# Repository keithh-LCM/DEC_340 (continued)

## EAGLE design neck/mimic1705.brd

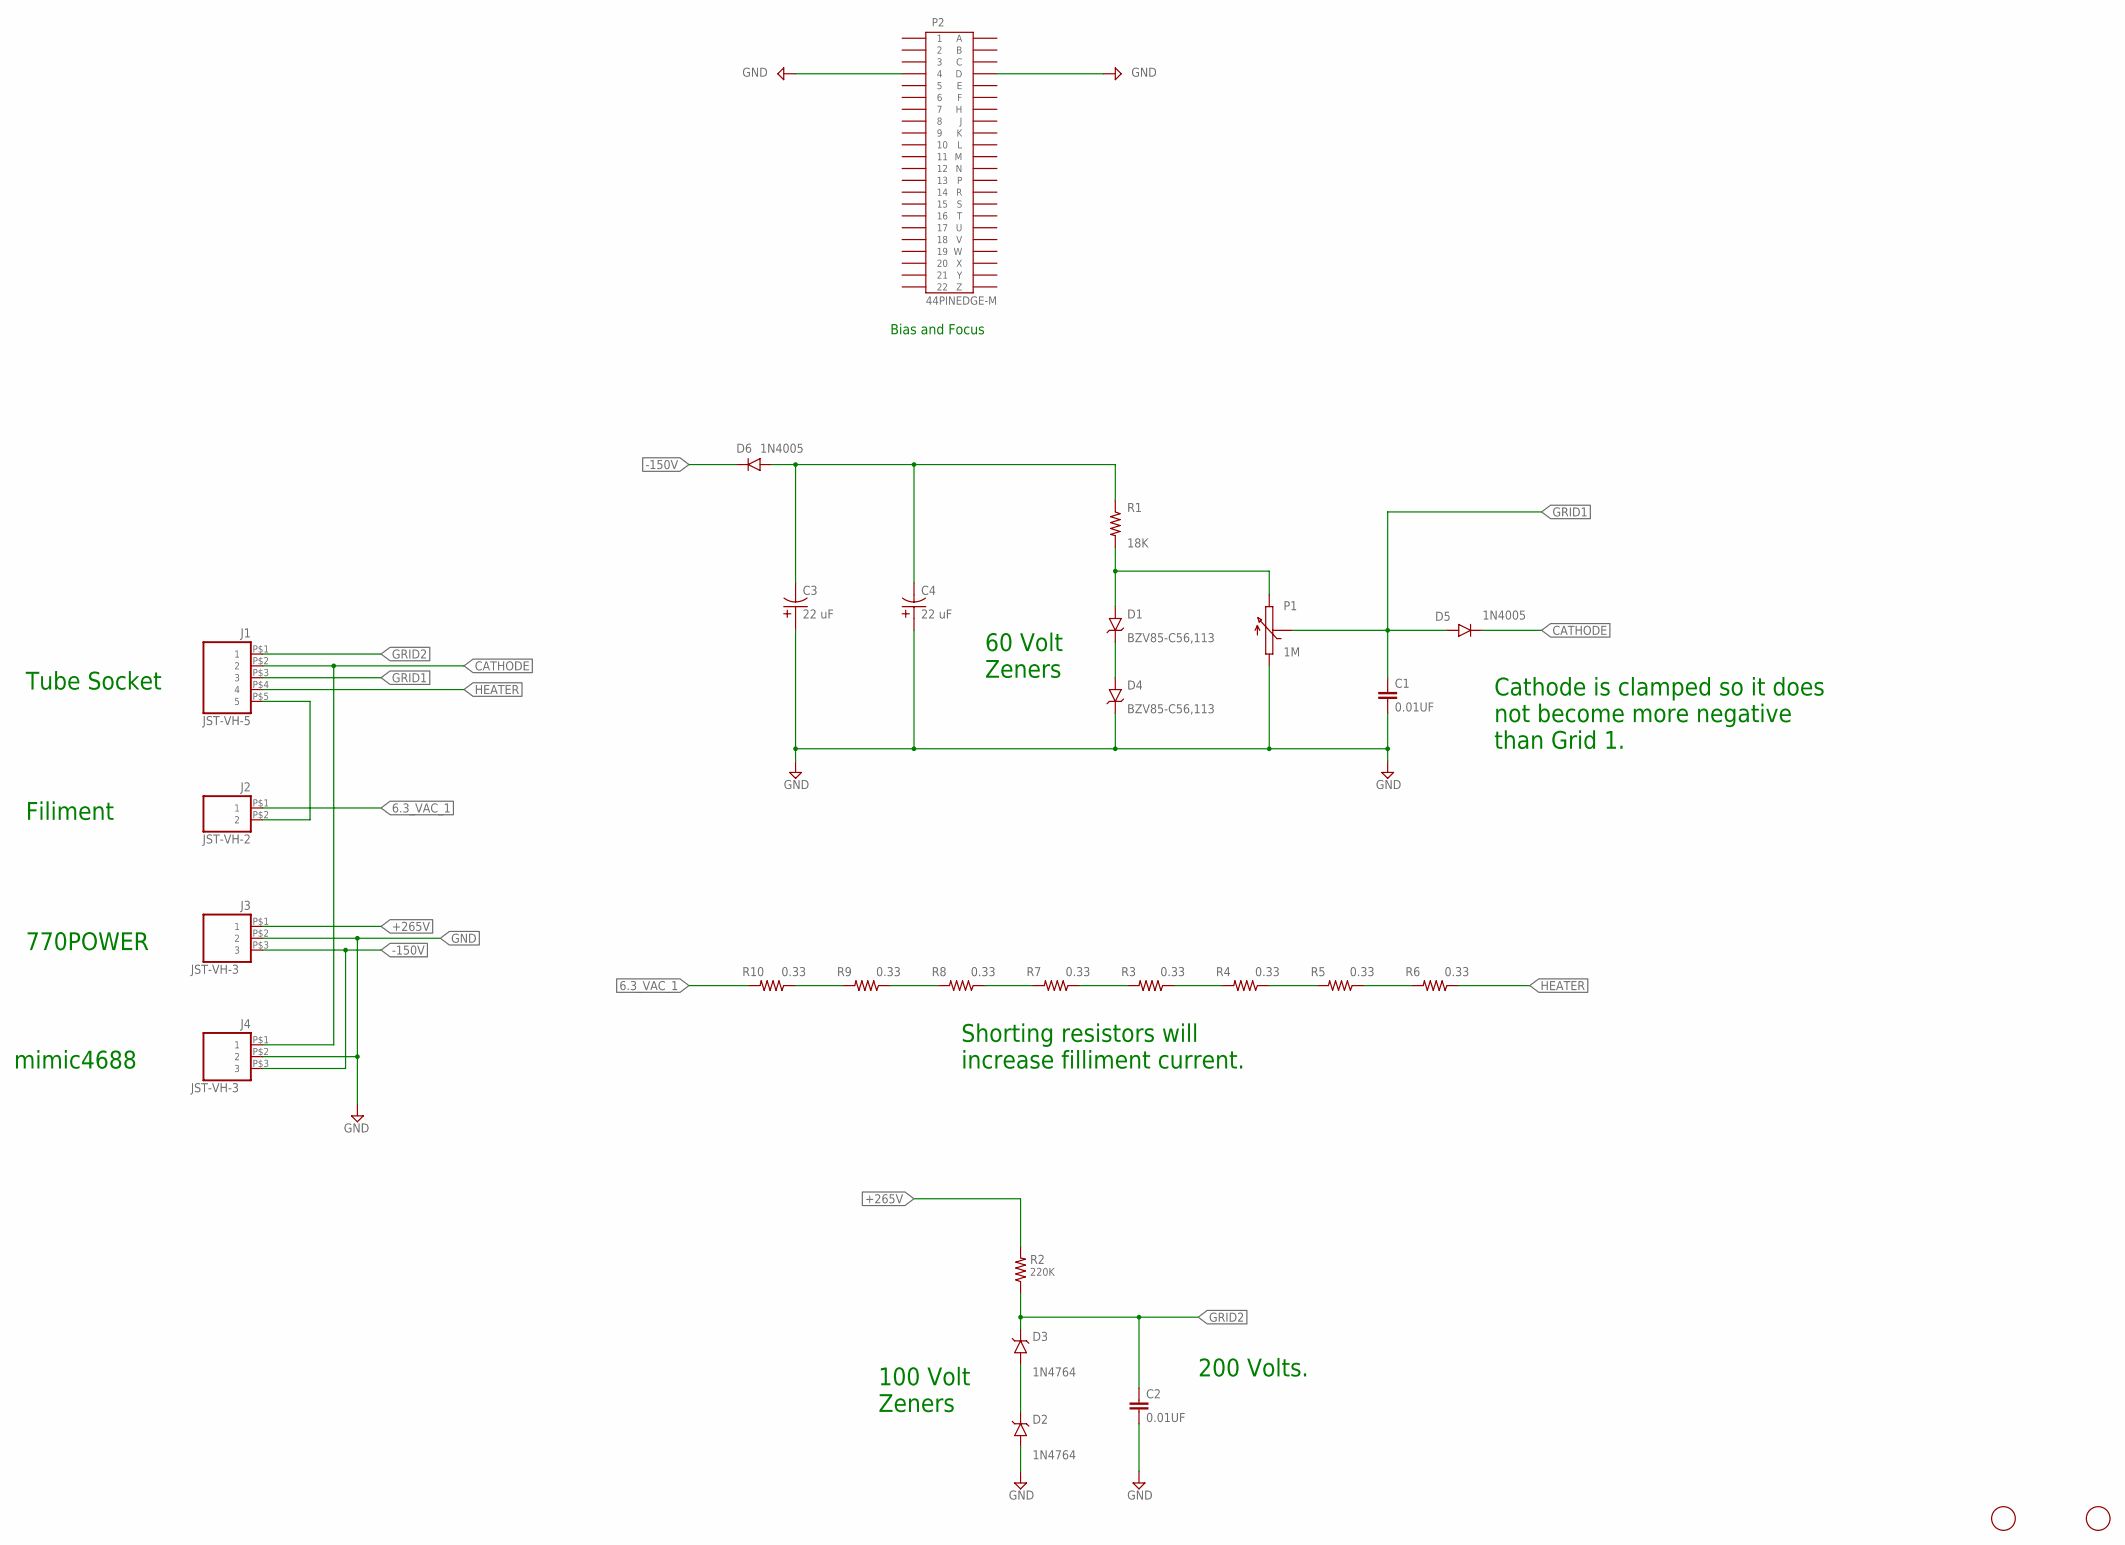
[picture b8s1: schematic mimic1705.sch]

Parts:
C1, C2: 0.01UF; 5MM_TH
C3, C4: 22 uF; AXIAL10X26
D1, D4: BZV85-C56,113; DO-41-10
D2, D3: 1N4764; DO-41-10
D5, D6: 1N4005; DO-41-10
J1: JST-VH-5; VHR-5N
J2: JST-VH-2; VHR-2N
J3, J4: JST-VH-3; VHR-3N
P1: 1M; 3006P
P2: 44PINEDGE-M; 44PINEDGE
R1: 18K; 0207/10
R2: 220K; 0207/10
R3, R4, R5, R6, R7, R8, R9, R10: 0.33; 0309/12
U$1, U$2: FIDUCIAL; FIDUCIAL_1MM

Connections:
6.3_VAC_1: J2.P$1 (1), R10.2
6.3_VAC_2: J1.P$5 (5), J2.P$2 (2)
+265V: J3.P$1 (1), R2.2
-150V: D6.C, J3.P$3 (3), J4.P$3 (3)
CATHODE: D5.C, J1.P$2 (2), J4.P$1 (1)
GND: C1.2, C2.2, C3.P$1 (1), C4.P$1 (1), D2.A, D4.C, J3.P$2 (2), J4.P$2 (2), P1.1, P2.4, P2.D
GRID1: C1.1, D5.A, J1.P$3 (3), P1.2
GRID2: C2.1, D3.C, J1.P$1 (1), R2.1
HEATER: J1.P$4 (4), R6.1
unnamed: D1.C, D4.A
unnamed: D2.C, D3.A
unnamed: R9.2, R10.1
unnamed: D1.A, P1.3, R1.2
unnamed: C3.P$2 (2), C4.P$2 (2), D6.A, R1.1
unnamed: R8.2, R9.1
unnamed: R7.2, R8.1
unnamed: R3.2, R7.1
unnamed: R3.1, R4.2
unnamed: R4.1, R5.2
unnamed: R5.1, R6.2

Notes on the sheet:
770POWER
Tube Socket
Cathode is clamped so it does not become more negative than Grid 1.
200 Volts.
Shorting resistors will increase filliment current.
mimic4688
Filiment
100 Volt Zeners
60 Volt Zeners
Bias and Focus

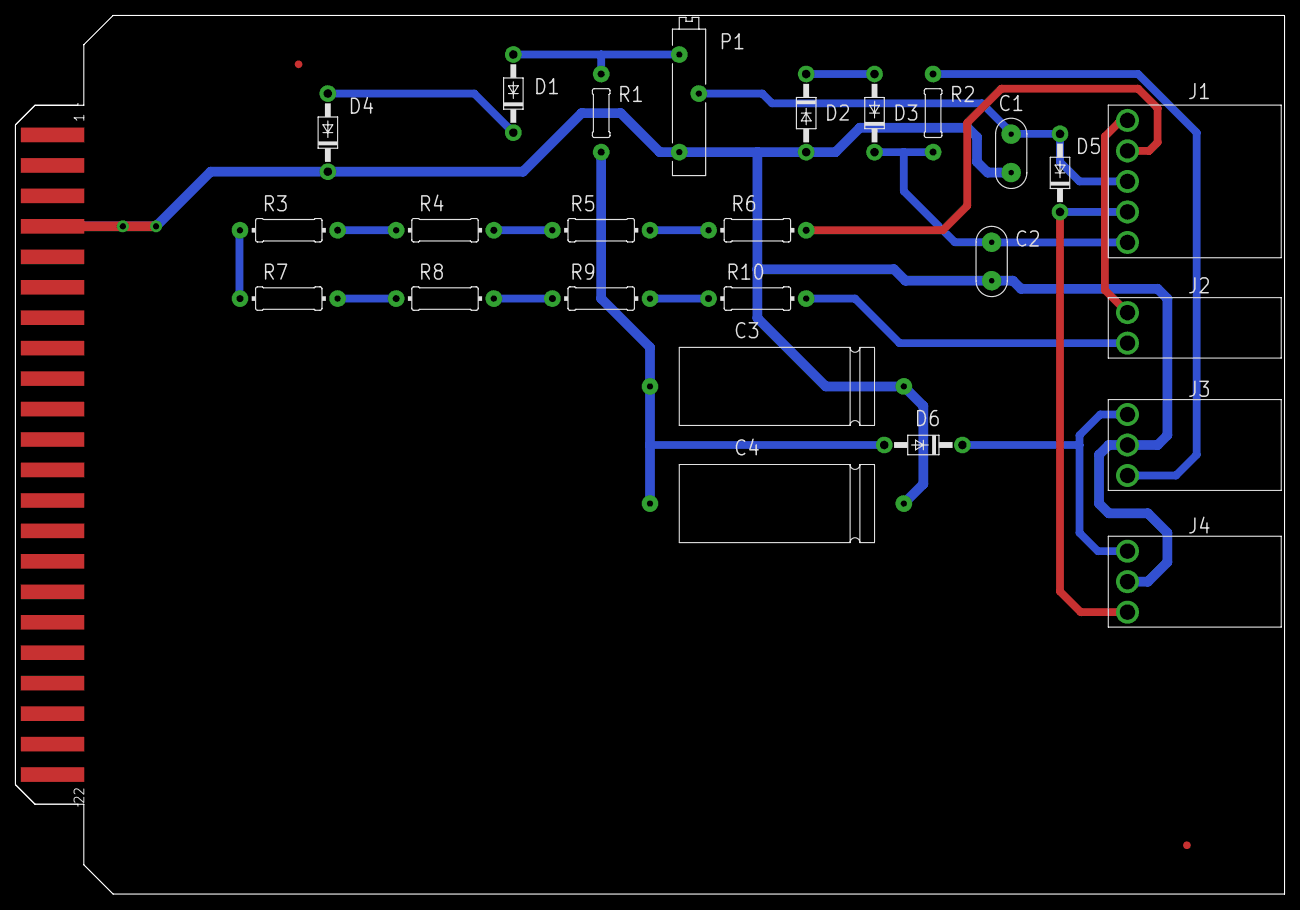
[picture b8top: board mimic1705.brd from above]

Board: 2 copper layers, 165.1 x 114.3 mm, 28 parts (0 on the bottom side), 20 nets.

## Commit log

2018-06-26 Eagle files added.
2018-06-26 xtra directory added.
2018-06-26 a comma for a test
2018-06-27 new commit
2018-06-28 files renamed
2018-06-28 files renamed again
2018-06-28 missing directory added
2018-06-29 modifed amplifier
2018-06-29 added darlington file
2018-06-29 test
2018-07-05 working on wire harness
2018-07-05 directories changed
2018-07-05 fixed ignore file
2018-07-05 delected some auto backup
2018-07-06 more work
2018-07-07 more changes
2018-07-09 A demo
2018-07-09 LTspice files added
2018-07-10 update netlist
2018-07-11 added file
2018-07-11 going to lunch
2018-07-12 EOD backup
2018-07-12 backplane metal added
2018-07-12 git ignore added
2018-07-12 removed file
2018-07-13 new file
2018-07-18 backup
2018-07-18 deleted file
2018-07-20 new .brd files
2018-07-24 preamplifier card being routed
2018-07-25 D/A being routed
2018-07-28 Friday backup
2018-08-01 end of day
2018-08-11 card layouts finished
2018-08-15 added logo
2018-08-16 generated gerbers
2018-08-22 revised artwork
2018-09-17 added missing connector on bckplane
